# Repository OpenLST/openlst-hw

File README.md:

OpenLST Reference Hardware
==========================

This repository contains a KiCad project with a hardware reference
implementation for the OpenLST.  This design is a simplified version
of the Texas Instruments CC1110 432 MHz reference design.  A 1 watt
power amplifier module has been added to increase operating range.
The design is intended for use at 437 MHz, however, it may be modified
for use at other frequencies.

The user is responsible for obtaining and maintaining the necessary
license to operate this radio.  The example project uses frequencies
in the US Amateur Radio UHF band. Transmissions in this band require a
valid FCC license and compliance with CFR Part 97.

Contents
--------

This repository contains the following items:

  * [KiCAD 4.0](https://kicad.org/) project with self-contained part library
  * [Schematic](pdf/openlst-hw.pdf) in PDF form
  * [Bill of materials](bom/) with ordering information for components
  * [Gerber files](gerber/) for PCB fabrication

License & Legal Information
---------------------------

Copyright 2018 Planet Labs Inc. This work is licensed under a
Creative Commons Attribution-ShareAlike 4.0 International License.

This document may contain technology or software the export of which
is or may be restricted by the Export Administration Act and the
Export Administration Regulations (EAR), 15 C.F.R. parts
730-774. Diversion contrary to U.S. law is prohibited.

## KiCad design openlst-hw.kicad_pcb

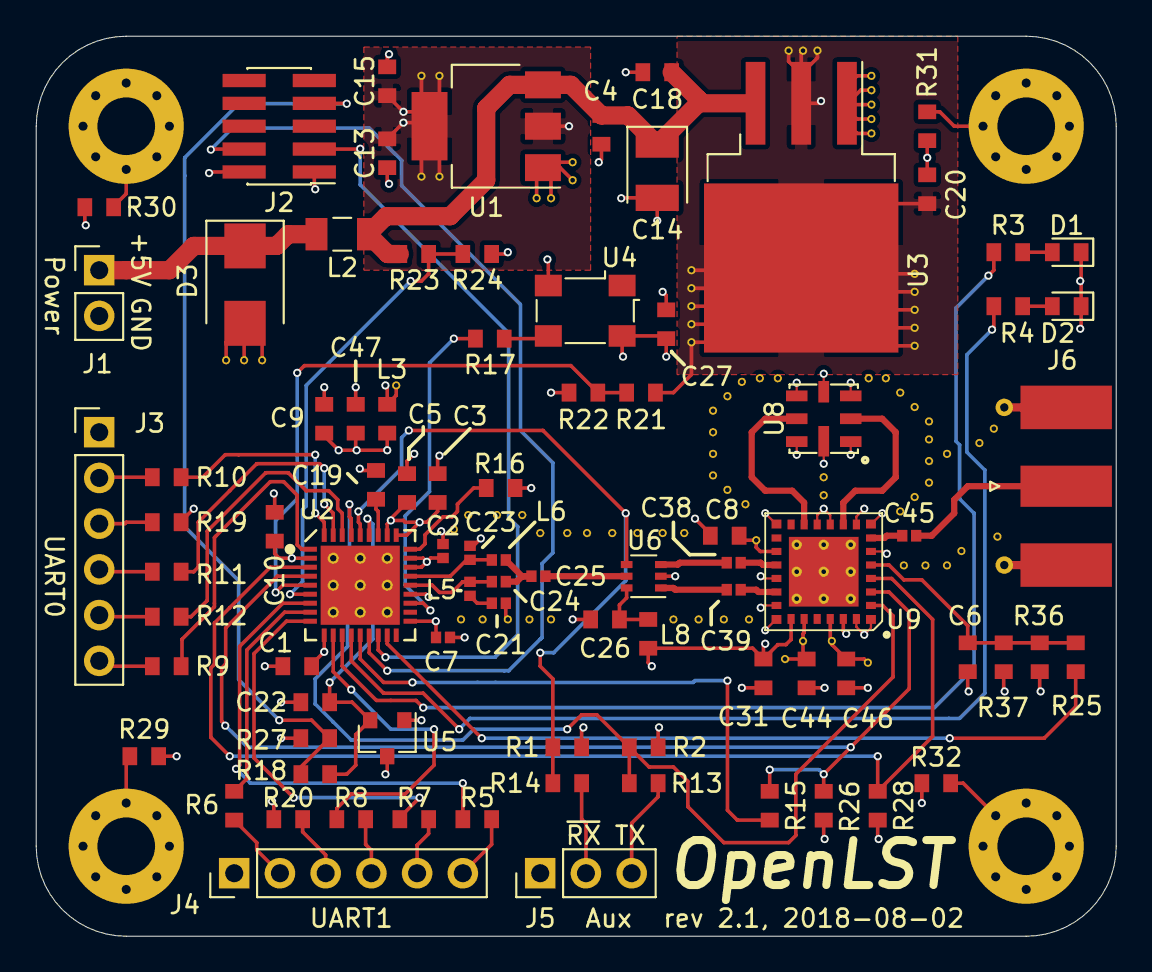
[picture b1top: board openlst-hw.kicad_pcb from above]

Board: 4 copper layers, 60.0 x 50.0 mm, 90 parts (0 on the bottom side), 65 nets.

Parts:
C1, C3, C5, C6, C8, C10, C15, C26, C27, C31: 0.1u; C_0603_1608Metric
C2, C7, C21, C25, C38, C39, C45: 220p; C_0402_1005Metric
C4, C13, C18, C20: 10u; C_0603_1608Metric
C9, C44, C46, C47: 1u; C_0603_1608Metric
C14: 100u; CP_EIA-3528-15_AVX-H
C19, C22: 1n; C_0603_1608Metric
C23, C24: 3.9p; C_0402_1005Metric
D1, D2: LED; LED_0603_1608Metric
D3: STPS340U; D_SMB
J1: 5VDC; PinHeader_1x02_P2.54mm_Vertical
J2: CC Prog/Debug; PinHeader_2x05_P1.27mm_Vertical_SMD
J3: UART0; PinHeader_1x06_P2.54mm_Vertical
J4: UART1; PinHeader_1x06_P2.54mm_Vertical
J5: Control Outputs; PinHeader_1x03_P2.54mm_Vertical
J6: ANT; SMA_Molex_73251-1153_EdgeMount_Horizontal
L2: Z=500 @ 100M; L_1206_3216Metric
L3, L8: Z=1k @ 100M; L_0603_1608Metric
L5, L6: 27n; L_0402_1005Metric
MK1, MK2, MK3, MK4: M3_Hole; MountingHole_3.2mm_M3_Pad_Via
R1, R2, R3, R4, R18, R26, R28: 1K; R_0603_1608Metric
R5, R6, R7, R8, R9, R10, R11, R12, R13, R14, R17: 100; R_0603_1608Metric
R15, R19, R20, R25, R29, R30, R31, R32: DNI; R_0603_1608Metric
R16: 56K; R_0603_1608Metric
R21, R23, R27: 33K; R_0603_1608Metric
R22, R24: 10K; R_0603_1608Metric
R36: 5K6; R_0603_1608Metric
R37: 3K3; R_0603_1608Metric
U1: LM1117-3.3; SOT-223-3_TabPin2
U2: CC1110; TI_CC_QFN36
U3: LT1086-3.6; TO-263-3_TabPin2
U4: FOX924 27MHz; Oscillator_SMD_Fordahl_DFAS15-4Pin_5.0x3.2mm
U5: TLV803S; SOT-23
U6: PE4259; SOT-363_SC-70-6
U8: STA1120A; SAW-8_3.8mm
U9: RFFM6403; Qorvo_LGA_28_ThermalVias

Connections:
+3V3: C13.1, C15.1, C27.1, C31.1, J2.2, L3.1, L8.1, R1.1, R19.1, R20.1, R26.1, R27.2, U1.2, U4.4, U5.3, U9.23
+5V: C4.1, C14.1, C18.1, L2.1, R23.2, U1.3, U3.3
/3V3_FILT: C1.1, C2.1, C3.1, C5.1, C7.1, C9.2, C10.1, C47.2, L3.2, U2.2, U2.10, U2.19, U2.22, U2.25, U2.26, U2.28, U2.29
/AN0: R21.1, R22.2, U2.5
/AN1: R23.1, R24.2, U2.6
/LST_TX_MODE: R2.2, R13.1, U2.33, U9.2
/PA_VAPC: C6.1, R25.1, R36.1, R37.2, U9.5
/PROG_DC: J2.3, U2.16
/PROG_DD: J2.4, U2.15
/RF_BYP: R28.1, U2.3, U9.4
/RF_EN: R15.1, R26.2, U2.4, U9.3
/UART0_CTS: J3.6, R9.2
/UART0_RTS: J3.2, R10.2
/UART0_RX: J3.4, R11.2
/UART0_TX: J3.5, R12.2
/UART1_CTS: J4.6, R5.2
/UART1_RTS: J4.2, R6.2
/UART1_RX: J4.4, R8.2
/UART1_TX: J4.5, R7.2
/~LST_RESET: J2.7, R18.2, R27.1
/~LST_RX_MODE: R1.2, R14.1, U2.32, U6.4
GND: C1.2, C2.2, C3.2, C4.2, C5.2, C6.2, C7.2, C8.2, C9.1, C10.2, C13.2, C14.2, C15.2, C18.2, C19.2, C20.2, C21.1, C22.2, C23.1, C26.2, C27.2, C31.2, C44.2, C46.2, C47.1, D1.1, D2.1, D3.2, J1.2, J2.1, J3.1, J4.1, J5.1, J6.2, R2.1, R16.1, R22.1, R24.1, R28.2, R29.1, R30.1, R31.1, R32.1, R36.2, U1.1, U2.37, U3.1, U4.2, U5.1, U6.2, U8.1, U8.3, U8.4, U8.5, U8.7, U8.8, U9.1, U9.6, U9.8, U9.9, U9.11, U9.12, U9.15, U9.19, U9.21, U9.22, U9.27, U9.28, U9.29
unnamed: C19.1, U2.30
unnamed: C21.2, L5.1
unnamed: C22.1, R18.1, U2.31, U5.2
unnamed: C23.2, L6.1, U2.24
unnamed: C24.1, L5.2, U2.23
unnamed: C24.2, C25.1, L6.2
unnamed: C25.2, U6.5
unnamed: C26.1, L8.2, U6.6
unnamed: C38.1, U6.3
unnamed: C38.2, U9.18
unnamed: C39.1, U6.1
unnamed: C39.2, U9.20
unnamed: C45.1, J6.1
unnamed: C45.2, U9.7
unnamed: D1.2, R3.1
unnamed: D2.2, R4.1
unnamed: D3.1, J1.1, L2.2
unnamed: J3.3, R19.2
unnamed: J4.3, R20.2
unnamed: J5.2, R14.2
unnamed: J5.3, R13.2
unnamed: MK1.1, R29.2
unnamed: MK2.1, R30.2
unnamed: MK3.1, R31.2
unnamed: MK4.1, R32.2
unnamed: R3.2, U2.12
unnamed: R4.2, U2.13
unnamed: R5.1, U2.7
unnamed: R6.1, U2.8
unnamed: R7.1, U2.9
unnamed: R8.1, U2.11
unnamed: R9.1, U2.1
unnamed: R10.1, U2.36
unnamed: R11.1, U2.35
unnamed: R12.1, U2.34
unnamed: R15.2, U2.14
unnamed: R16.2, U2.27
unnamed: R17.1, U4.3
unnamed: R17.2, U2.21
unnamed: R25.2, U2.17
unnamed: U8.2, U9.10
unnamed: U8.6, U9.13
VCC_3V6: C8.1, C20.1, C44.1, C46.1, R21.2, R37.1, U3.2, U9.17, U9.24, U9.26

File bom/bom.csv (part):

Reference, Value, Footprint, Datasheet, Manuf, ManufPN, Supplier, SupplierPN
"L6","27n","Inductor_SMD:L_0402_1005Metric","http://search.murata.co.jp/Ceramy/image/img/P02/JELF243A-0050.pdf","Murata","LQW15AN27NJ00D","Digikey","490-1151-1-ND"
"J6","ANT","Connector_Coaxial:SMA_Molex_73251-1153_EdgeMount_Horizontal","https://www.molex.com/pdm_docs/sd/732511150_sd.pdf","Molex","732511150","Digikey","WM5534-ND"
"C45","220p","Capacitor_SMD:C_0402_1005Metric","https://api.kemet.com/component-edge/download/datasheet/C040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","Kemet","C0402C221J2GACAUTO","Digikey","399-11552-1-ND"
"C25","220p","Capacitor_SMD:C_0402_1005Metric","https://api.kemet.com/component-edge/download/datasheet/C040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","Kemet","C0402C221J2GACAUTO","Digikey","399-11552-1-ND"
"C24","3.9p","Capacitor_SMD:C_0402_1005Metric","http://search.murata.co.jp/Ceramy/image/img/A01X/G101/ENG/GJ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","Murata","GJM1555C1H3R9CB01D","Digikey","490-3097-1-ND"
"L5","27n","Inductor_SMD:L_0402_1005Metric","http://search.murata.co.jp/Ceramy/image/img/P02/JELF243A-0050.pdf","Murata","LQW15AN27NJ00D","Digikey","490-1151-1-ND"
"C21","220p","Capacitor_SMD:C_0402_1005Metric","https://api.kemet.com/component-edge/download/datasheet/C040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","Kemet","C0402C221J2GACAUTO","Digikey","399-11552-1-ND"
"U1","LM1117-3.3","Package_TO_SOT_SMD:SOT-223-3_TabPin2","http://www.ti.com/lit/ds/symlink/lm1117.pdf","Texas Instruments","LM1117IMP-3.3/NOPB","Digikey","LM1117IMP-3.3/NOPBCT-ND"
"C4","10u","Capacitor_SMD:C_0603_1608Metric","http://search.murata.co.jp/Ceramy/image/img/A01X/G101/ENG/GR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","Murata","GRT188C81A106ME13D","Digikey","490-12283-1-ND"
"C13","10u","Capacitor_SMD:C_0603_1608Metric","http://search.murata.co.jp/Ceramy/image/img/A01X/G101/ENG/GR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","Murata","GRT188C81A106ME13D","Digikey","490-12283-1-ND"
"C15","0.1u","Capacitor_SMD:C_0603_1608Metric","http://datasheets.avx.com/AutoMLCC.pdf","AVX","0603YC104K4T4A","Digikey","478-9382-1-ND"
"J1","5VDC","Connector_PinHeader_2.54mm:PinHeader_1x02_P2.54mm_Vertical",""
"D3","STPS340U","Diode_SMD:D_SMB","http://www.st.com/content/ccc/resource/technical/document/da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","STMicroelectronics","STPS340U","Digikey","497-2465-1-ND"
"L2","Z=500 @ 100M","Inductor_SMD:L_1206_3216Metric","https://assets.lairdtech.com/home/brandworld/files/MI1206L50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","Laird","MI1206L501R-10","Digikey","240-2407-1-ND"
"C14","100u","Capacitor_Tantalum_SMD:CP_EIA-3528-15_AVX-H","http://datasheets.avx.com/TPS.pdf","AVX","TPSB107M010R0400","Digikey","478-5231-1-ND"
"U3","LT1086-3.6","Package_TO_SOT_SMD:TO-263-3_TabPin2","http://www.linear.com/docs/1722","Linear","LT1086CM-3.6#PBF","Digikey","LT1086CM-3.6#PBF-ND"
"C46","1u","Capacitor_SMD:C_0603_1608Metric","http://www.samsungsem.com/kr/support/product-search/mlcc/CL1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","Samsung","CL10B105MO8NNWC","Digikey","1276-6524-6-ND"
"C44","1u","Capacitor_SMD:C_0603_1608Metric","http://www.samsungsem.com/kr/support/product-search/mlcc/CL1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","Samsung","CL10B105MO8NNWC","Digikey","1276-6524-6-ND"
"U6","PE4259","Package_TO_SOT_SMD:SOT-363_SC-70-6","http://www.psemi.com/pdf/datasheets/pe4259ds.pdf","pSemi","4259-63","Digikey","1046-1011-1-ND"
"C38","220p","Capacitor_SMD:C_0402_1005Metric","https://api.kemet.com/component-edge/download/datasheet/C040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","Kemet","C0402C221J2GACAUTO","Digikey","399-11552-1-ND"
"C39","220p","Capacitor_SMD:C_0402_1005Metric","https://api.kemet.com/component-edge/download/datasheet/C040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","Kemet","C0402C221J2GACAUTO","Digikey","399-11552-1-ND"
"C26","0.1u","Capacitor_SMD:C_0603_1608Metric","http://datasheets.avx.com/AutoMLCC.pdf","AVX","0603YC104K4T4A","Digikey","478-9382-1-ND"
"U2","CC1110","openlst:TI_CC_QFN36","http://www.ti.com/lit/ds/symlink/cc1110-cc1111.pdf","Texas Instruments","CC1110F32RHHR","Digikey","296-38560-1-ND"
"U5","TLV803S","Package_TO_SOT_SMD:SOT-23","http://www.ti.com/lit/ds/symlink/tlv803.pdf","Texas Instruments","TLV803SDBZR","Digikey","296-29196-1-ND"
"R18","1K","Resistor_SMD:R_0603_1608Metric","http://www.yageo.com/documents/recent/PYu-RC_Group_51_RoHS_L_9.pdf","Yageo","RC0603JR-071KL","Digikey","311-1.0KGRCT-ND"
"C22","1n","Capacitor_SMD:C_0603_1608Metric","https://www.murata.com/~/media/webrenewal/support/library/ca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","Murata","GCM188R71E102KA37D","Digikey","490-8016-1-ND"
"R16","56K","Resistor_SMD:R_0603_1608Metric","https://www.seielect.com/Catalog/SEI-RMCF_RMCP.pdf","Stackpole","RMCF0603FT56K0","Digikey","RMCF0603FT56K0CT-ND"
"C19","1n","Capacitor_SMD:C_0603_1608Metric","https://www.murata.com/~/media/webrenewal/support/library/ca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","Murata","GCM188R71E102KA37D","Digikey","490-8016-1-ND"
"J2","CC Prog/Debug","Connector_PinHeader_1.27mm:PinHeader_2x05_P1.27mm_Vertical_SMD","http://suddendocs.samtec.com/prints/ftsh-1xx-xx-xxx-dv-xxx-x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","Samtec","FTSH-105-01-L-DV-K-P","Digikey","SAM9076-ND"
"R5","100","Resistor_SMD:R_0603_1608Metric","http://www.yageo.com/NewPortal/yageodocoutput?fileName=/pdf/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","Yageo","AC0603FR-07100RL","Digikey","YAG3561CT-ND"
"R6","100","Resistor_SMD:R_0603_1608Metric","http://www.yageo.com/NewPortal/yageodocoutput?fileName=/pdf/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","Yageo","AC0603FR-07100RL","Digikey","YAG3561CT-ND"
"R7","100","Resistor_SMD:R_0603_1608Metric","http://www.yageo.com/NewPortal/yageodocoutput?fileName=/pdf/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","Yageo","AC0603FR-07100RL","Digikey","YAG3561CT-ND"
"R8","100","Resistor_SMD:R_0603_1608Metric","http://www.yageo.com/NewPortal/yageodocoutput?fileName=/pdf/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","Yageo","AC0603FR-07100RL","Digikey","YAG3561CT-ND"
"R9","100","Resistor_SMD:R_0603_1608Metric","http://www.yageo.com/NewPortal/yageodocoutput?fileName=/pdf/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","Yageo","AC0603FR-07100RL","Digikey","YAG3561CT-ND"
"R10","100","Resistor_SMD:R_0603_1608Metric","http://www.yageo.com/NewPortal/yageodocoutput?fileName=/pdf/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","Yageo","AC0603FR-07100RL","Digikey","YAG3561CT-ND"
"R11","100","Resistor_SMD:R_0603_1608Metric","http://www.yageo.com/NewPortal/yageodocoutput?fileName=/pdf/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","Yageo","AC0603FR-07100RL","Digikey","YAG3561CT-ND"
"R12","100","Resistor_SMD:R_0603_1608Metric","http://www.yageo.com/NewPortal/yageodocoutput?fileName=/pdf/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","Yageo","AC0603FR-07100RL","Digikey","YAG3561CT-ND"
"C31","0.1u","Capacitor_SMD:C_0603_1608Metric","http://datasheets.avx.com/AutoMLCC.pdf","AVX","0603YC104K4T4A","Digikey","478-9382-1-ND"
"R28","1K","Resistor_SMD:R_0603_1608Metric","http://www.yageo.com/documents/recent/PYu-RC_Group_51_RoHS_L_9.pdf","Yageo","RC0603JR-071KL","Digikey","311-1.0KGRCT-ND"
"R26","1K","Resistor_SMD:R_0603_1608Metric","http://www.yageo.com/documents/recent/PYu-RC_Group_51_RoHS_L_9.pdf","Yageo","RC0603JR-071KL","Digikey","311-1.0KGRCT-ND"
"R1","1K","Resistor_SMD:R_0603_1608Metric","http://www.yageo.com/documents/recent/PYu-RC_Group_51_RoHS_L_9.pdf","Yageo","RC0603JR-071KL","Digikey","311-1.0KGRCT-ND"
"R2","1K","Resistor_SMD:R_0603_1608Metric","http://www.yageo.com/documents/recent/PYu-RC_Group_51_RoHS_L_9.pdf","Yageo","RC0603JR-071KL","Digikey","311-1.0KGRCT-ND"
"U4","FOX924 27MHz","Oscillator:Oscillator_SMD_Fordahl_DFAS15-4Pin_5.0x3.2mm","http://www.foxonline.com/pdfs/fox924.pdf","Fox Electronics","FT5HNBPK27.0-T1","Digikey","631-1075-1-ND"
"R17","100","Resistor_SMD:R_0603_1608Metric","http://www.yageo.com/NewPortal/yageodocoutput?fileName=/pdf/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","Yageo","AC0603FR-07100RL","Digikey","YAG3561CT-ND"
"C23","3.9p","Capacitor_SMD:C_0402_1005Metric","http://search.murata.co.jp/Ceramy/image/img/A01X/G101/ENG/GJ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","Murata","GJM1555C1H3R9CB01D","Digikey","490-3097-1-ND"
"C27","0.1u","Capacitor_SMD:C_0603_1608Metric","http://datasheets.avx.com/AutoMLCC.pdf","AVX","0603YC104K4T4A","Digikey","478-9382-1-ND"
"R15","DNI","Resistor_SMD:R_0603_1608Metric",""
"D1","LED","LED_SMD:LED_0603_1608Metric","http://katalog.we-online.de/led/datasheet/150060VS75000.pdf","Wurth","150060VS75000","Digikey","732-4980-1-ND"
"R3","1K","Resistor_SMD:R_0603_1608Metric","http://www.yageo.com/documents/recent/PYu-RC_Group_51_RoHS_L_9.pdf","Yageo","RC0603JR-071KL","Digikey","311-1.0KGRCT-ND"
"D2","LED","LED_SMD:LED_0603_1608Metric","http://katalog.we-online.de/led/datasheet/150060SS75000.pdf","Wurth","150060SS75000","Digikey","732-4979-1-ND"
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
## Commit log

2018-08-03 Initial release
2021-11-08 Update README.md
    https://forum.kicad.info/t/warning-avoid-all-links-to-kicad-pcb-org-use-kicad-org/31521

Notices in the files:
openlst-hw.kicad_pcb:
International License (CC-BY-SA 4.0).
